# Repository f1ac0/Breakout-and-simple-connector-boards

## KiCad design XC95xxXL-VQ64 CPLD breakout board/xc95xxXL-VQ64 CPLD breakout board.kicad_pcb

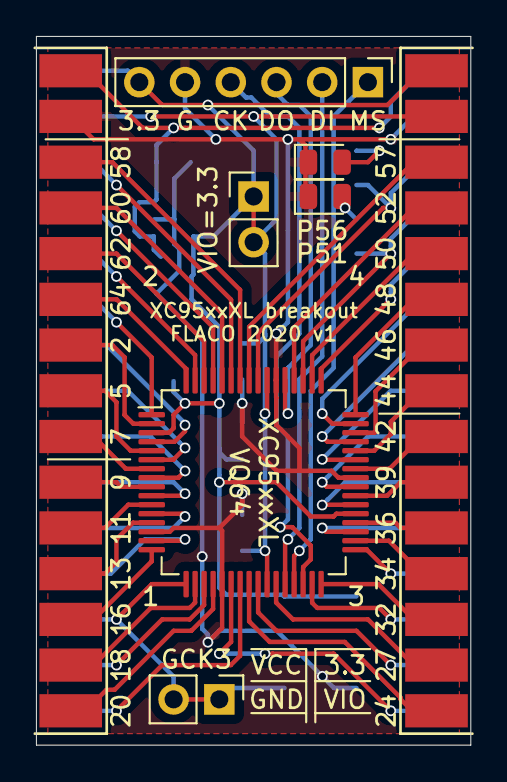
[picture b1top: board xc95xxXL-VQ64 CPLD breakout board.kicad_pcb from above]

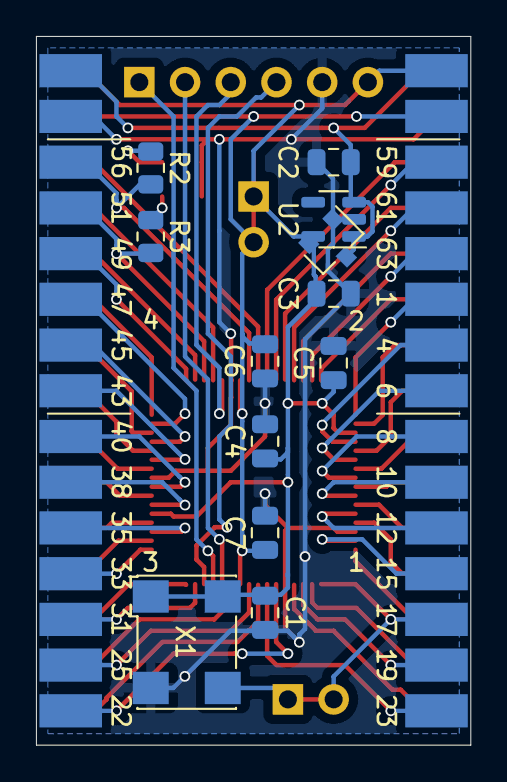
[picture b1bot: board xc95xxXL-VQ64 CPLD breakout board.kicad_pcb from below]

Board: 2 copper layers, 24.1 x 39.4 mm, 20 parts (12 on the bottom side), 62 nets.

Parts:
C1, C4, C5, C6, C7: 100n; C_0805_2012Metric
C2, C3: 1u; C_0805_2012Metric
D1: 4_15; LED_0805_2012Metric
D2: 4_10; LED_0805_2012Metric
J1: JTAG; PinHeader_1x06_P2.54mm_Vertical
J2: Block 1-2; Pin_Header_2x15_Male_EdgeMount_Pitch2.54mm
J3: Block 3-4; Pin_Header_2x15_Male_EdgeMount_Pitch2.54mm
JP1: GCK3; PinHeader_1x02_P2.54mm_Vertical
JP2: VCCIO; PinHeader_1x02_P2.54mm_Vertical
R2, R3: 2k; R_0805_2012Metric
U1: XC9572XL-VQ64; TQFP-64_10x10mm_P0.5mm
U2: SPX3819M5-L-3-3; SOT-23-5
U3: XC6206PxxxMR; SOT-23
X1: ASV-xxxMHz; Oscillator_SMD_Abracon_ASV-4Pin_7.0x5.1mm

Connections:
+3.3V: C1.1, C3.1, C4.1, C5.1, J1.6, J2.1, J3.30, JP2.1 (A), U1.3 (VCC), U1.37 (VCC), U2.5 (OUT), U3.2 (VO), X1.1 (EN), X1.4 (Vdd)
+5V: C2.1, J2.2, J3.29, U2.1 (IN), U2.3 (EN), U3.3 (VI)
/1_2: J2.17, U1.8
/1_3: J2.21, U1.12
/1_4: J2.24, U1.13
/1_5: J2.20, U1.9
/1_6: J2.19, U1.10
/1_8: J2.22, U1.11
/1_9: J2.23, U1.15 (I/O/GCK1)
/1_10: J2.28, U1.18
/1_11: J2.26, U1.16 (I/O/GCK2)
/1_12: J2.29, U1.23
/1_14: J2.25, JP1.1 (A), JP1.2 (B), U1.17 (I/O/GCK3), X1.3 (OUT)
/1_15: J2.27, U1.19
/1_17: J2.30, U1.20
/2_2: J2.8, U1.60
/2_3: J2.6, U1.58
/2_4: J2.5, U1.59
/2_5: J2.7, U1.61
/2_6: J2.10, U1.62
/2_8: J2.9, U1.63
/2_9: J2.12, U1.64 (I/O/GSR)
/2_10: J2.11, U1.1
/2_11: J2.14, U1.2 (I/O/GTS2)
/2_12: J2.13, U1.4
/2_14: J2.16, U1.5 (I/O/GTS1)
/2_15: J2.15, U1.6
/2_17: J2.18, U1.7
/3_2: J3.1, U1.22
/3_3: J3.5, U1.31
/3_4: J3.6, U1.32
/3_5: J3.2, U1.24
/3_6: J3.8, U1.34
/3_8: J3.3, U1.25
/3_9: J3.4, U1.27
/3_10: J3.12, U1.39
/3_11: J3.7, U1.33
/3_12: J3.13, U1.40
/3_14: J3.9, U1.35
/3_15: J3.10, U1.36
/3_16: J3.14, U1.42
/3_17: J3.11, U1.38
/4_2: J3.15, U1.43
/4_3: J3.18, U1.46
/4_4: J3.19, U1.47
/4_5: J3.16, U1.44
/4_6: J3.21, U1.49
/4_8: J3.17, U1.45
/4_10: J3.23, R3.1, U1.51
/4_11: J3.20, U1.48
/4_12: J3.24, U1.52
/4_14: J3.22, U1.50
/4_15: J3.25, R2.1, U1.56
/4_17: J3.26, U1.57
/TCK: J1.4, U1.30 (TCK)
/TDI: J1.2, U1.28 (TDI)
/TDO: J1.3, U1.53 (TDO)
/TMS: J1.1, U1.29 (TMS)
/VCCIO: C6.1, C7.1, J2.3, J3.28, JP2.2 (B), U1.26 (VCCIO), U1.55 (VCCIO)
GND: C1.2, C2.2, C3.2, C4.2, C5.2, C6.2, C7.2, D1.1 (K), D2.1 (K), J1.5, J2.4, J3.27, U1.14 (GND), U1.21 (GND), U1.41 (GND), U1.54 (GND), U2.2 (GND), U3.1 (GND), X1.2 (GND)
unnamed: D1.2 (A), R2.2
unnamed: D2.2 (A), R3.2

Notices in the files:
XC95xxXL-VQ64 CPLD breakout board/xc95xxXL-VQ64 CPLD breakout board.kicad_pcb:
FLACO 2019, licence of this PCB is CC-BY-NC-SA
